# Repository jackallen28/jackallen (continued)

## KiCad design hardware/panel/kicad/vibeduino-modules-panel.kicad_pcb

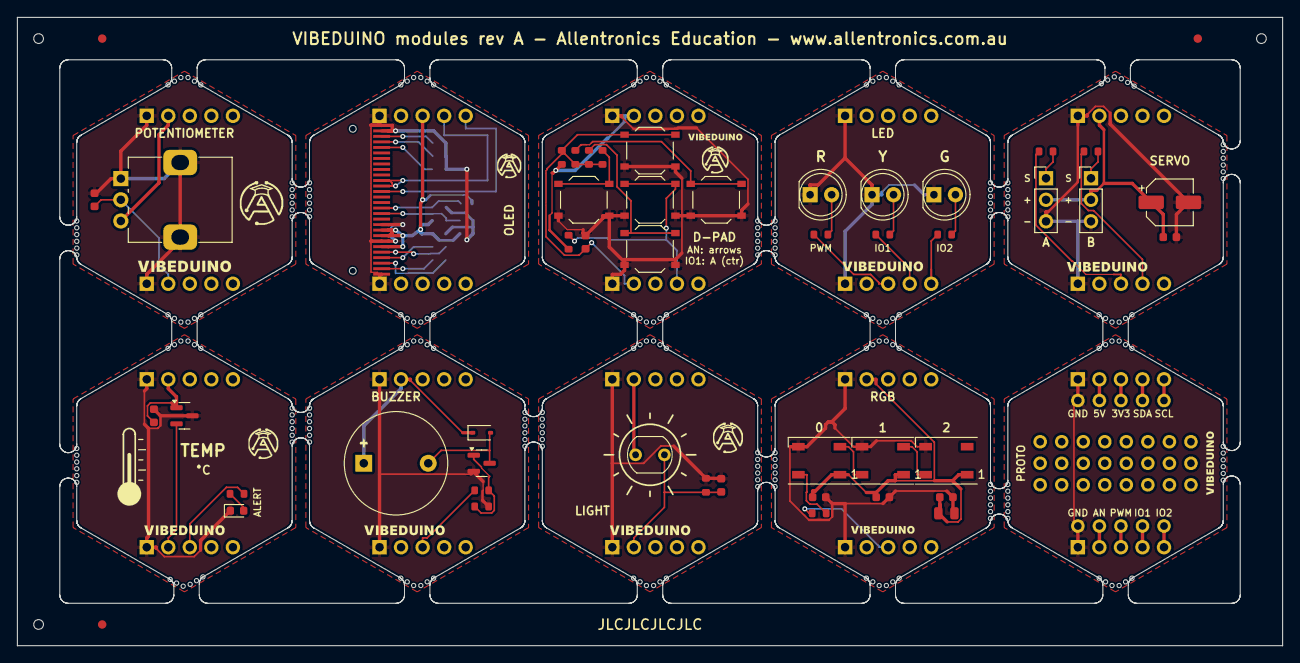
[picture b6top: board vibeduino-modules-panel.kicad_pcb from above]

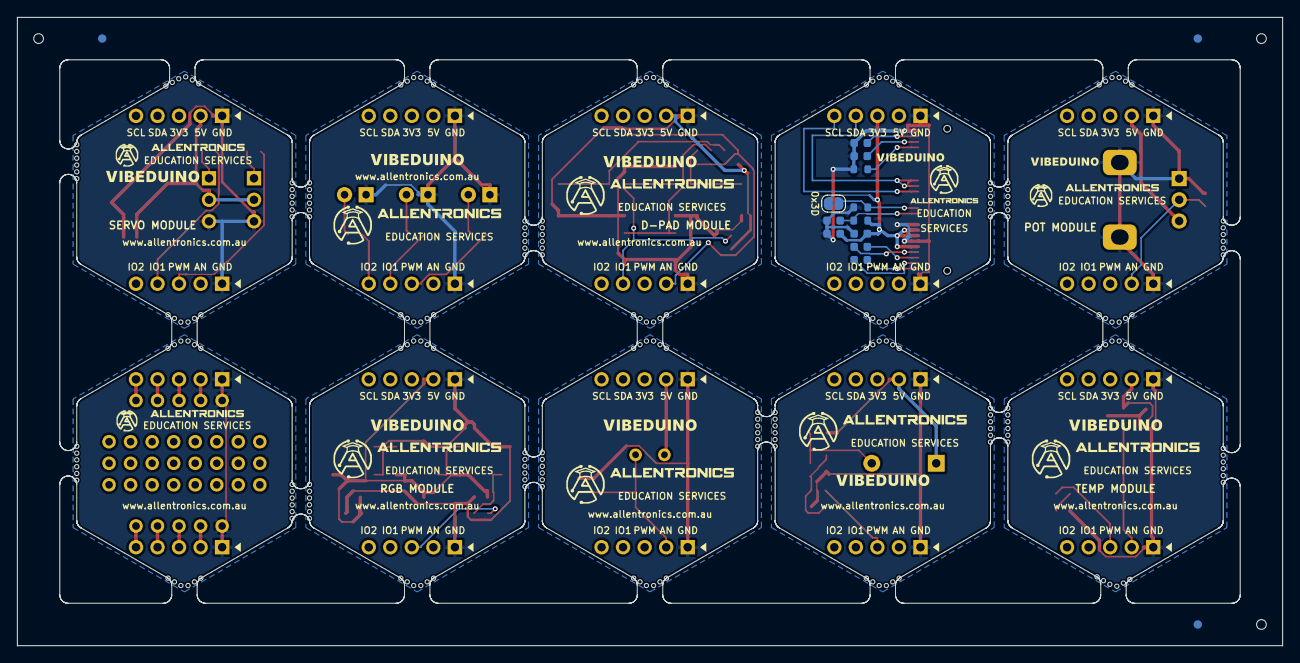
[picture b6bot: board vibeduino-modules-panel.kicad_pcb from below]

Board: 2 copper layers, 149.2 x 74.1 mm, 316 parts (34 on the bottom side), 64 nets.

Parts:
BZ1_BUZZER: 12mm passive 5V; Buzzer_12x9.5RM7.6
C1_DPAD, C1_LIGHT, C1_POT, C1_RGB, C1_TEMP, C2_RGB, C2_SERVO, C3_RGB, C6_OLED: 100nF; C_0603_1608Metric
C1_OLED: 2.2uF 16V; C_0603_1608Metric
C1_SERVO: 100uF 10V; CP_Elec_5x5.4
C2_OLED, C3_OLED, C4_OLED, C7_OLED: 1uF; C_0603_1608Metric
C4_RGB: 10uF; C_0805_2012Metric
C5_OLED: 4.7uF; C_0603_1608Metric
D1_BUZZER: 1N4148WS; D_SOD-323
D1_LED: 5mm RED diffused; LED_D5.0mm
D1_RGB, D2_RGB, D3_RGB: WS2812B; LED_WS2812B_PLCC4_5.0x5.0mm_P3.2mm
D1_TEMP: RED; LED_0603_1608Metric
D2_LED: 5mm YELLOW diffused; LED_D5.0mm
D3_LED: 5mm GREEN diffused; LED_D5.0mm
DS1_OLED: OLED 0.66in 64x48 SSD1306; OLED_0.66in_64x48_FPC28
J1_BUZZER, J1_DPAD, J1_LED, J1_LIGHT, J1_OLED, J1_POT, J1_PROTO, J1_RGB, J1_SERVO, J1_TEMP: BUS PWR/I2C; PinHeader_1x05_P2.54mm_Vertical
J2_BUZZER, J2_DPAD, J2_LED, J2_LIGHT, J2_OLED, J2_POT, J2_PROTO, J2_RGB, J2_SERVO, J2_TEMP: BUS SIGNALS; PinHeader_1x05_P2.54mm_Vertical
J3_SERVO: SERVO A; PinHeader_1x03_P2.54mm_Vertical
J4_SERVO: SERVO B; PinHeader_1x03_P2.54mm_Vertical
JP1_OLED: ADDR 0x3D; SolderJumper-2_P1.3mm_Open_RoundedPad1.0x1.5mm
KiKit_FID_B_1, KiKit_FID_B_2, KiKit_FID_B_3: Fiducial
KiKit_FID_T_1, KiKit_FID_T_2, KiKit_FID_T_3: Fiducial
KiKit_MB_1_1, KiKit_MB_1_2, KiKit_MB_1_3, KiKit_MB_1_4, KiKit_MB_1_5, KiKit_MB_1_6, KiKit_MB_2_1, KiKit_MB_2_2, KiKit_MB_2_3, KiKit_MB_2_4, KiKit_MB_2_5, KiKit_MB_2_6, KiKit_MB_3_1, KiKit_MB_3_2, KiKit_MB_3_3, KiKit_MB_3_4, KiKit_MB_3_5, KiKit_MB_3_6, KiKit_MB_4_1, KiKit_MB_4_2, KiKit_MB_4_3, KiKit_MB_4_4, KiKit_MB_4_5, KiKit_MB_4_6, KiKit_MB_5_1, KiKit_MB_5_2, KiKit_MB_5_3, KiKit_MB_5_4, KiKit_MB_5_5, KiKit_MB_5_6, KiKit_MB_6_1, KiKit_MB_6_2, KiKit_MB_6_3, KiKit_MB_6_4, KiKit_MB_6_5, KiKit_MB_6_6, KiKit_MB_7_1, KiKit_MB_7_2, KiKit_MB_7_3, KiKit_MB_7_4, KiKit_MB_7_5, KiKit_MB_7_6, KiKit_MB_8_1, KiKit_MB_8_2, KiKit_MB_8_3, KiKit_MB_8_4, KiKit_MB_8_5, KiKit_MB_8_6, KiKit_MB_9_1, KiKit_MB_9_2, KiKit_MB_9_3, KiKit_MB_9_4, KiKit_MB_9_5, KiKit_MB_9_6, KiKit_MB_10_1, KiKit_MB_10_2, KiKit_MB_10_3, KiKit_MB_10_4, KiKit_MB_10_5, KiKit_MB_10_6, KiKit_MB_11_1, KiKit_MB_11_2, KiKit_MB_11_3, KiKit_MB_11_4, KiKit_MB_11_5, KiKit_MB_11_6, KiKit_MB_12_1, KiKit_MB_12_2, KiKit_MB_12_3, KiKit_MB_12_4, KiKit_MB_12_5, KiKit_MB_12_6, KiKit_MB_13_1, KiKit_MB_13_2, KiKit_MB_13_3, KiKit_MB_13_4, KiKit_MB_13_5, KiKit_MB_13_6, KiKit_MB_14_1, KiKit_MB_14_2, KiKit_MB_14_3, KiKit_MB_14_4, KiKit_MB_14_5, KiKit_MB_14_6, KiKit_MB_15_1, KiKit_MB_15_2, KiKit_MB_15_3, KiKit_MB_15_4, KiKit_MB_15_5, KiKit_MB_15_6, KiKit_MB_16_1, KiKit_MB_16_2, KiKit_MB_16_3, KiKit_MB_16_4, KiKit_MB_16_5, KiKit_MB_16_6, KiKit_MB_17_1, KiKit_MB_17_2, KiKit_MB_17_3, KiKit_MB_17_4, KiKit_MB_17_5, KiKit_MB_17_6, KiKit_MB_18_1, KiKit_MB_18_2, KiKit_MB_18_3, KiKit_MB_18_4, KiKit_MB_18_5, KiKit_MB_18_6, KiKit_MB_19_1, KiKit_MB_19_2, KiKit_MB_19_3, KiKit_MB_19_4, KiKit_MB_19_5, KiKit_MB_19_6, KiKit_MB_20_1, KiKit_MB_20_2, KiKit_MB_20_3, KiKit_MB_20_4, KiKit_MB_20_5, KiKit_MB_20_6, KiKit_MB_21_1, KiKit_MB_21_2, KiKit_MB_21_3, KiKit_MB_21_4, KiKit_MB_21_5, KiKit_MB_21_6, KiKit_MB_22_1, KiKit_MB_22_2, KiKit_MB_22_3, KiKit_MB_22_4, KiKit_MB_22_5, KiKit_MB_22_6, KiKit_MB_23_1, KiKit_MB_23_2, KiKit_MB_23_3, KiKit_MB_23_4, KiKit_MB_23_5, KiKit_MB_23_6, KiKit_MB_24_1, KiKit_MB_24_2, KiKit_MB_24_3, KiKit_MB_24_4, KiKit_MB_24_5, KiKit_MB_24_6, KiKit_MB_25_1, KiKit_MB_25_2, KiKit_MB_25_3, KiKit_MB_25_4, KiKit_MB_25_5, KiKit_MB_25_6, KiKit_MB_26_1, KiKit_MB_26_2, KiKit_MB_26_3, KiKit_MB_26_4, KiKit_MB_26_5, KiKit_MB_26_6, KiKit_MB_27_1, KiKit_MB_27_2, KiKit_MB_27_3, KiKit_MB_27_4, KiKit_MB_27_5, KiKit_MB_27_6, KiKit_MB_28_1, KiKit_MB_28_2, KiKit_MB_28_3, KiKit_MB_28_4, KiKit_MB_28_5, KiKit_MB_28_6, KiKit_MB_29_1, KiKit_MB_29_2, KiKit_MB_29_3, KiKit_MB_29_4, KiKit_MB_29_5, KiKit_MB_29_6, KiKit_MB_30_1, KiKit_MB_30_2, KiKit_MB_30_3, KiKit_MB_30_4, KiKit_MB_30_5, KiKit_MB_30_6, KiKit_MB_31_1, KiKit_MB_31_2, KiKit_MB_31_3, KiKit_MB_31_4, KiKit_MB_31_5, KiKit_MB_31_6, KiKit_MB_32_1, KiKit_MB_32_2, KiKit_MB_32_3, KiKit_MB_32_4, KiKit_MB_32_5, KiKit_MB_32_6, KiKit_MB_33_1, KiKit_MB_33_2, KiKit_MB_33_3, KiKit_MB_33_4, KiKit_MB_33_5, KiKit_MB_33_6, KiKit_MB_34_1, KiKit_MB_34_2, KiKit_MB_34_3, KiKit_MB_34_4, KiKit_MB_34_5, KiKit_MB_34_6, KiKit_MB_35_1, KiKit_MB_35_2, KiKit_MB_35_3, KiKit_MB_35_4, KiKit_MB_35_5, KiKit_MB_35_6, KiKit_MB_36_1, KiKit_MB_36_2, KiKit_MB_36_3, KiKit_MB_36_4, KiKit_MB_36_5, KiKit_MB_36_6, KiKit_MB_37_1, KiKit_MB_37_2, KiKit_MB_37_3, KiKit_MB_37_4, KiKit_MB_37_5, KiKit_MB_37_6, KiKit_MB_38_1, KiKit_MB_38_2, KiKit_MB_38_3, KiKit_MB_38_4, KiKit_MB_38_5, KiKit_MB_38_6: NPTH
KiKit_TO_1, KiKit_TO_2, KiKit_TO_3: NPTH
PF1_PROTO: 2.54 GRID; ProtoGrid
Q1_BUZZER: MMBT3904; SOT-23
R1_BUZZER, R1_TEMP, R2_DPAD: 1k; R_0603_1608Metric
R1_DPAD, R2_BUZZER, R2_LIGHT, R2_OLED, R3_OLED, R4_DPAD, R5_DPAD: 10k; R_0603_1608Metric
R1_LED, R2_LED, R3_LED: 470R; R_0603_1608Metric
R1_LIGHT: GL5528 LDR; R_LDR_5.1x4.3mm_P3.4mm_Vertical
R1_OLED: 390k; R_0603_1608Metric
R1_RGB: 330R; R_0603_1608Metric
R1_SERVO, R2_SERVO: 220R; R_0603_1608Metric
R3_DPAD: 3.3k; R_0603_1608Metric
RV1_POT: 10k lin; Potentiometer_Alps_RK09K_Single_Vertical
SW1_DPAD: UP; SW_Push_1P1T_XKB_TS-1187A
SW2_DPAD: RIGHT; SW_Push_1P1T_XKB_TS-1187A
SW3_DPAD: DOWN; SW_Push_1P1T_XKB_TS-1187A
SW4_DPAD: LEFT; SW_Push_1P1T_XKB_TS-1187A
SW5_DPAD: A; SW_Push_1P1T_XKB_TS-1187A
TP1_PROTO: BUS BREAKOUT; BusBreakout
U1_TEMP: MCP9700A-E/TT; SOT-23

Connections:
BUZZER-+5V: BZ1_BUZZER.1, D1_BUZZER.1, J1_BUZZER.2
BUZZER-BZ_B: Q1_BUZZER.1, R1_BUZZER.2, R2_BUZZER.1
BUZZER-BZ_N: BZ1_BUZZER.2, D1_BUZZER.2, Q1_BUZZER.3
BUZZER-GND: J1_BUZZER.1, J2_BUZZER.1, Q1_BUZZER.2, R2_BUZZER.2
BUZZER-PWM: J2_BUZZER.3, R1_BUZZER.1
DPAD-+5V: J1_DPAD.2, R1_DPAD.1, R5_DPAD.1
DPAD-AN: C1_DPAD.1, J2_DPAD.2, R1_DPAD.2, R2_DPAD.1, R3_DPAD.1, R4_DPAD.1, SW1_DPAD.1
DPAD-DP_D: R3_DPAD.2, SW3_DPAD.1
DPAD-DP_L: R4_DPAD.2, SW4_DPAD.1
DPAD-DP_R: R2_DPAD.2, SW2_DPAD.1
DPAD-GND: C1_DPAD.2, J1_DPAD.1, J2_DPAD.1, SW1_DPAD.2, SW2_DPAD.2, SW3_DPAD.2, SW4_DPAD.2, SW5_DPAD.2
DPAD-IO1: J2_DPAD.4, R5_DPAD.2, SW5_DPAD.1
LED-GND: D1_LED.1, D2_LED.1, D3_LED.1, J1_LED.1, J2_LED.1
LED-IO1: J2_LED.4, R2_LED.1
LED-IO2: J2_LED.5, R3_LED.1
LED-LED_G: D3_LED.2, R3_LED.2
LED-LED_R: D1_LED.2, R1_LED.2
LED-LED_Y: D2_LED.2, R2_LED.2
LED-PWM: J2_LED.3, R1_LED.1
LIGHT-+5V: J1_LIGHT.2, R1_LIGHT.1
LIGHT-AN: C1_LIGHT.1, J2_LIGHT.2, R1_LIGHT.2, R2_LIGHT.1
LIGHT-GND: C1_LIGHT.2, J1_LIGHT.1, J2_LIGHT.1, R2_LIGHT.2
OLED-+3V3: C4_OLED.1, C6_OLED.1, DS1_OLED.6, DS1_OLED.8, DS1_OLED.9, J1_OLED.3, JP1_OLED.2, R2_OLED.1
OLED-C1N: C2_OLED.2, DS1_OLED.5
OLED-C1P: C2_OLED.1, DS1_OLED.4
OLED-C2N: C3_OLED.2, DS1_OLED.3
OLED-C2P: C3_OLED.1, DS1_OLED.2
OLED-GND: C1_OLED.2, C4_OLED.2, C5_OLED.2, C6_OLED.2, C7_OLED.2, DS1_OLED.1, DS1_OLED.7, DS1_OLED.10, DS1_OLED.27, DS1_OLED.28, J1_OLED.1, J2_OLED.1, R1_OLED.2, R3_OLED.2
OLED-IREF: DS1_OLED.24, R1_OLED.1
OLED-OLED_RES: C7_OLED.1, DS1_OLED.12, R2_OLED.2
OLED-OLED_SA0: DS1_OLED.13, JP1_OLED.1, R3_OLED.1
OLED-SCL: DS1_OLED.16, J1_OLED.5
OLED-SDA: DS1_OLED.17, DS1_OLED.18, J1_OLED.4
OLED-VCC: C1_OLED.1, DS1_OLED.26
OLED-VCOMH: C5_OLED.1, DS1_OLED.25
POT-+5V: J1_POT.2, RV1_POT.3
POT-AN: C1_POT.1, J2_POT.2, RV1_POT.2
POT-GND: C1_POT.2, J1_POT.1, J2_POT.1, RV1_POT.1, RV1_POT.MP
PROTO-+3V3: J1_PROTO.3, TP1_PROTO.J13
PROTO-+5V: J1_PROTO.2, TP1_PROTO.J12
PROTO-AN: J2_PROTO.2, TP1_PROTO.J22
PROTO-GND: J1_PROTO.1, J2_PROTO.1, TP1_PROTO.J11, TP1_PROTO.J21
PROTO-IO1: J2_PROTO.4, TP1_PROTO.J24
PROTO-IO2: J2_PROTO.5, TP1_PROTO.J25
PROTO-PWM: J2_PROTO.3, TP1_PROTO.J23
PROTO-SCL: J1_PROTO.5, TP1_PROTO.J15
PROTO-SDA: J1_PROTO.4, TP1_PROTO.J14
RGB-+5V: C1_RGB.1, C2_RGB.1, C3_RGB.1, C4_RGB.1, D1_RGB.1, D2_RGB.1, D3_RGB.1, J1_RGB.2
RGB-GND: C1_RGB.2, C2_RGB.2, C3_RGB.2, C4_RGB.2, D1_RGB.3, D2_RGB.3, D3_RGB.3, J1_RGB.1, J2_RGB.1
RGB-PWM: J2_RGB.3, R1_RGB.1
RGB-RGB_D1: D1_RGB.2, D2_RGB.4
RGB-RGB_D2: D2_RGB.2, D3_RGB.4
RGB-RGB_DIN: D1_RGB.4, R1_RGB.2
SERVO-+5V: C1_SERVO.1, C2_SERVO.1, J1_SERVO.2, J3_SERVO.2, J4_SERVO.2
SERVO-GND: C1_SERVO.2, C2_SERVO.2, J1_SERVO.1, J2_SERVO.1, J3_SERVO.3, J4_SERVO.3
SERVO-IO1: J2_SERVO.4, R2_SERVO.1
SERVO-PWM: J2_SERVO.3, R1_SERVO.1
SERVO-SRV_A: J3_SERVO.1, R1_SERVO.2
SERVO-SRV_B: J4_SERVO.1, R2_SERVO.2
TEMP-+5V: C1_TEMP.1, J1_TEMP.2, U1_TEMP.1
TEMP-AN: J2_TEMP.2, U1_TEMP.2
TEMP-GND: C1_TEMP.2, D1_TEMP.1, J1_TEMP.1, J2_TEMP.1, U1_TEMP.3
TEMP-LED_A: D1_TEMP.2, R1_TEMP.2
TEMP-PWM: J2_TEMP.3, R1_TEMP.1

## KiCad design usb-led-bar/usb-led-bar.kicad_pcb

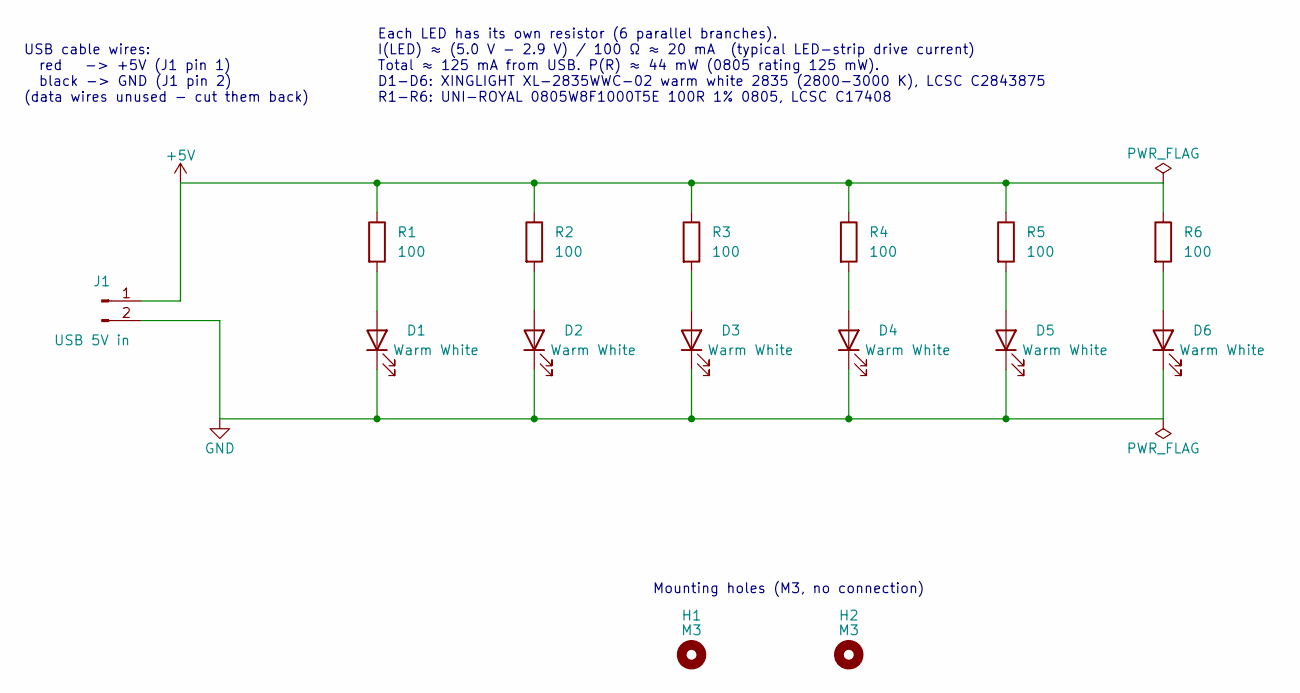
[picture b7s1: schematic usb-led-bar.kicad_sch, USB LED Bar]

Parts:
D1, D2, D3, D4, D5, D6: Warm White; LED_2835_PolarityTolerant; MPN XL-2835WWC-02; LCSC C2843875
H1, H2: M3; MountingHole_3.2mm_M3
J1: USB 5V in; USB_Power_Wires_1x02_P6mm_Relief
R1, R2, R3, R4, R5, R6: 100; R_0805_2012Metric; MPN 0805W8F1000T5E; LCSC C17408

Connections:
+5V: J1.1, R1.1, R2.1, R3.1, R4.1, R5.1, R6.1
GND: D1.1 (K), D2.1 (K), D3.1 (K), D4.1 (K), D5.1 (K), D6.1 (K), J1.2
unnamed: D1.2 (A), R1.2
unnamed: D2.2 (A), R2.2
unnamed: D3.2 (A), R3.2
unnamed: D4.2 (A), R4.2
unnamed: D5.2 (A), R5.2
unnamed: D6.2 (A), R6.2

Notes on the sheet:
USB cable wires: red -> +5V (J1 pin 1) black -> GND (J1 pin 2) (data wires unused - cut them back)
Each LED has its own resistor (6 parallel branches). I(LED) ≈ (5.0 V - 2.9 V) / 100 Ω ≈ 20 mA (typical LED-strip drive current) Total ≈ 125 mA from USB. P(R) ≈ 44 mW (0805 rating 125 mW). D1-D6: XINGLIGHT XL-2835WWC-02 warm white 2835 (2800-3000 K), LCSC C2843875 R1-R6: UNI-ROYAL 0805W8F1000T5E 100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
Mounting holes (M3, no connection)

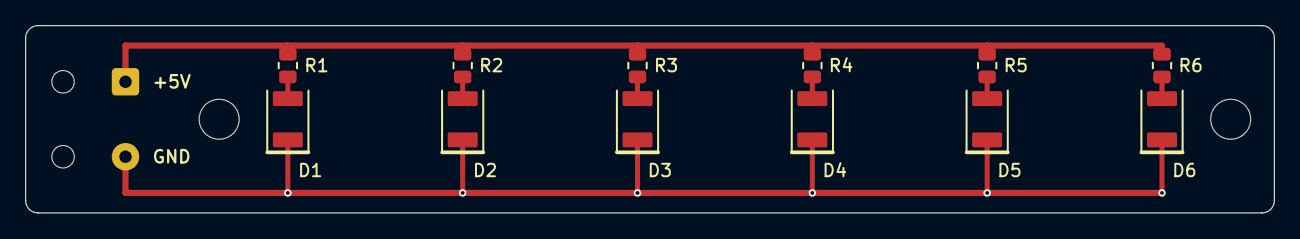
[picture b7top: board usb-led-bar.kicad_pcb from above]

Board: 2 copper layers, 100.0 x 15.0 mm, 15 parts (0 on the bottom side), 8 nets.

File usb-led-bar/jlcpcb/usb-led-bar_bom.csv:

Comment,Designator,Footprint,LCSC Part #
Warm White XL-2835WWC-02,"D1,D2,D3,D4,D5,D6",LED_2835_PolarityTolerant,C2843875
100 0805W8F1000T5E,"R1,R2,R3,R4,R5,R6",R_0805_2012Metric,C17408

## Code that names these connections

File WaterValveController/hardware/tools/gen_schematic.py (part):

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                desc='Q1 gate pull-up: the valve is off unless Q2 pulls the gate down')
    s.wire(r18['pins']['1'], (58.42, 124.46), (S_[0], 124.46))
    s.junction((S_[0], 124.46))
    gate = r18['pins']['2']
    s.wire(gate, G)
    q2 = s.add('Transistor_FET:2N7000', 'Q2', '2N7000', 55.88, 147.32, fp=FP_TO92,
               ref_at=(60.96, 146.05), val_at=(60.96, 148.59),
               desc='Logic-level N-MOSFET that drives the Q1 gate from D8')
    s.wire(q2['pins']['D'], gate)
    s.junction(gate)
    s.wire(q2['pins']['S'], (q2['pins']['S'][0], 157.48))
    s.power('GND', (q2['pins']['S'][0], 157.48), show=False)
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    s.wire(r20['pins']['2'], (49.53, 157.48))
    s.power('GND', (49.53, 157.48), show=False)
    s.wire(r19['pins']['1'], (36.83, 147.32))
    s.label('VALVE', (36.83, 147.32), 180)
    d2 = s.add('Device:D', 'D2', '1N5408', 78.74, 146.05, rot=270, fp=FP_D,
               ref_at=(76.2, 144.78), val_at=(76.2, 147.32), ref_just='right', val_just='right',
               desc='Flyback diode across the valve output: clamps the switch-off spike')
    s.wire(D_, (D_[0], 142.24), (78.74, 142.24), (86.36, 142.24), (96.52, 142.24))
    s.junction((78.74, 142.24))
    s.wire((78.74, 142.24), d2['pins']['K'])
    s.label('SOL_OUT', (86.36, 142.24))
    s.wire(d2['pins']['A'], (78.74, 157.48))
    s.power('GND', (78.74, 157.48), show=False)
    j3 = s.add('Connector:Screw_Terminal_01x04', 'J3', 'VALVE / FLOW', 101.6, 144.78, fp=FP_TB4,
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    s.wire(Q['3'], (88.9, Q['3'][1]))
    s.power('+5V', (88.9, Q['3'][1]), rot=90)
    s.wire(Q['4'], (91.44, Q['4'][1]))
    s.label('FLOW_IN', (91.44, Q['4'][1]), 180)
    c6 = s.add('Device:C', 'C6', '100nF', 116.84, 146.05, fp=FP_C, desc='Sensor supply decoupling, at J3')
    s.power('+5V', c6['pins']['1'])
    s.power('GND', c6['pins']['2'], show=False)
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    s.text('FLOW SENSOR INPUT (YF-G1, NPN open collector)', (20.32, 165.1), 2, True)
    node_in = (30.48, 180.34)
    s.wire((22.86, node_in[1]), node_in)
    s.label('FLOW_IN', (22.86, node_in[1]), 180)
    r1 = s.add('Device:R', 'R1', '10k', 30.48, 175.26, fp=FP_R, desc='Flow signal pull-up')
    s.power('+5V', r1['pins']['1'])
    s.wire(r1['pins']['2'], node_in)
    r2 = s.add('Device:R', 'R2', '1k', 39.37, node_in[1], rot=90, fp=FP_R,
               ref_at=(39.37, node_in[1] - 2.54), val_at=(39.37, node_in[1] + 2.54), ref_just='center',
               val_just='center', desc='Flow signal series resistor (RC filter / pin protection)')
    s.wire(node_in, r2['pins']['1'])
    s.junction(node_in)
    node_f = (48.26, node_in[1])
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    s.junction(node_f)
    s.wire(c5['pins']['2'], (48.26, 189.23))
    s.power('GND', (48.26, 189.23), show=False)
    s.label('FLOW', (55.88, node_f[1]), 0)
    s.text('R2 + C5 filter fast spikes (time constant 10 us);\nthe firmware also ignores pulses < 2 ms apart.',
           (66.04, 177.8))

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               desc='Panel push button (MODE / CAL): 1 = button, 2 = GND. JST-XH 2-pin')
    s.wire((281.94, nb[1]), nb, j5['pins']['1'])
    s.junction(nb)
    s.label('BTN', (281.94, nb[1]), 180)
    s.wire(j5['pins']['2'], (307.34, j5['pins']['2'][1]))
    s.power('GND', (307.34, j5['pins']['2'][1]), rot=270, show=False)
    for i, (lbl, jref, rref) in enumerate((('LED25', 'J6', 'R4'), ('LED50', 'J7', 'R5'), ('LED100', 'J8', 'R6'))):
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    r11 = s.add('Device:R', 'R11', '1.8k', 299.72, 160.02, fp=FP_R, ref_at=(297.18, 158.75), val_at=(297.18, 161.29),
                ref_just='right', val_just='right', desc='Data to ESP divider (top)')
    s.wire((299.72, 153.67), r11['pins']['1'])
    s.label('TX_5V', (299.72, 153.67), 90)
    node_e = r11['pins']['2']
    r12 = s.add('Device:R', 'R12', '3.3k', 299.72, 167.64, fp=FP_R, ref_at=(297.18, 166.37), val_at=(297.18, 168.91),
                ref_just='right', val_just='right', desc='Data to ESP divider (bottom), 5 V -> 3.24 V')
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    s.wire(Q['2'], (332.74, Q['2'][1]))
    s.power('GND', (332.74, Q['2'][1]), rot=270, show=False)
    s.wire(node_e, (312.42, node_e[1]), (Q['3'][0], node_e[1]))
    s.label('TO_ESP', (312.42, node_e[1]))
    s.junction(node_e)
    r21 = s.add('Device:R', 'R21', '1k', 326.39, Q['4'][1], rot=90, fp=FP_R,
                ref_at=(326.39, Q['4'][1] + 2.54), val_at=(326.39, Q['4'][1] + 5.08), ref_just='center',
                val_just='center', desc='Data from ESP: series resistor (pin protection)')
    s.wire(Q['4'], r21['pins']['2'])
    s.wire(r21['pins']['1'], (314.96, Q['4'][1]))
    s.label('ESP_IN', (314.96, Q['4'][1]), 180)

    s.text('MOUNTING HOLES (M4)', (358.14, 147.32), 2, True)
    for i in range(4):
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               on_board=False, in_bom=False, ref_at=(95.25, 214.63), val_at=(95.25, 217.17),
               desc='Existing 12 V DC normally-closed solenoid valve')
    s.wire(sv['pins']['1'], (91.44, 205.74), (83.82, 205.74))
    s.label('SOL_OUT', (83.82, 205.74), 180)
    s.wire(sv['pins']['2'], (91.44, 226.06))
    s.power('GND', (91.44, 226.06), show=False)
    fs = s.add('WaterValve:YF-G1_Flow_Sensor', 'FS1', 'YF-G1 (64.8 pulses/L)', 137.16, 215.9,
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    s.wire(F['1'], (152.4, F['1'][1]), (152.4, 210.82))
    s.power('+5V', (152.4, 210.82))
    s.wire(F['2'], (154.94, F['2'][1]))
    s.label('FLOW_IN', (154.94, F['2'][1]), 0)
    s.wire(F['3'], (152.4, F['3'][1]), (152.4, 223.52))
    s.power('GND', (152.4, 223.52), show=False)
    sw1 = s.add('Switch:SW_Push', 'SW1', 'MODE / CAL', 38.1, 243.84, on_board=False,
                ref_at=(38.1, 236.22), val_at=(38.1, 238.76), ref_just='center', val_just='center',
                desc='Panel momentary push button (normally open), with a JST-XH 2-pin lead to J5')
    s.wire(sw1['pins']['1'], (27.94, 243.84))
    s.label('BTN', (27.94, 243.84), 180)
    s.wire(sw1['pins']['2'], (48.26, 243.84), (48.26, 248.92))
    s.power('GND', (48.26, 248.92), show=False)
    for i, (lbl, ref, colour) in enumerate((('LED25', 'D3', 'green'), ('LED50', 'D4', 'yellow'),
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        '(company "Arduino Nano carrier board")',
        '(comment 1 "YF-G1 flow sensor, MOSFET valve driver, RX480E 433 MHz receiver, ESP link")',
        '(comment 2 "Firmware: WaterValveController.ino")',
        '(comment 3 "Pins: D2 flow, D4 button, D5-D7 LEDs, D8 valve, D11/D12 ESP, A0-A3 remote")',
    ]
    return s, title

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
